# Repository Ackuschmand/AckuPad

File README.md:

# AckuPad

Programmable Makropad based on a Seeed XIAO RP2040 with 6 switches, a toggle switch, an OLED display and a rotary encoder!

---

## Bill of Materials

### Electronics
- 1× Seeed XIAO RP2040  
- 7× MX-Style switches  
  (6× normal buttons, 1× mode button)
- 1× EC11 Rotary encoder  
- 1x 0.91 inch OLED displays  
- 1× PCB  

---

### Mechanical
- 1× 3D printed case (top)  
- 1× 3D printed case (bottom)
- 1× 3D printed case (middle)
- 1× Encoder knob
- 7× Blank DSA keycaps
- 4× M3x16mm screws
- 4× M3x5mx4mm heatset inserts
---

## Notes

- The mode button is a **normal mechanical keyboard switch**
- Buttons and encoder are **PC-controlled**
- Firmware does not contain fixed macros
- Case is fully 3D printed
- Custom PCB is used

---

## Files

- `RP2040 Code.ino` – firmware  
- `AckuPad UI.ahk` – PC script  
- PCB and CAD files are in their respective folders

---

## Pictures

PCB:

Circuit diagram:

Case:

Finished AckuPad:

Youtube video:

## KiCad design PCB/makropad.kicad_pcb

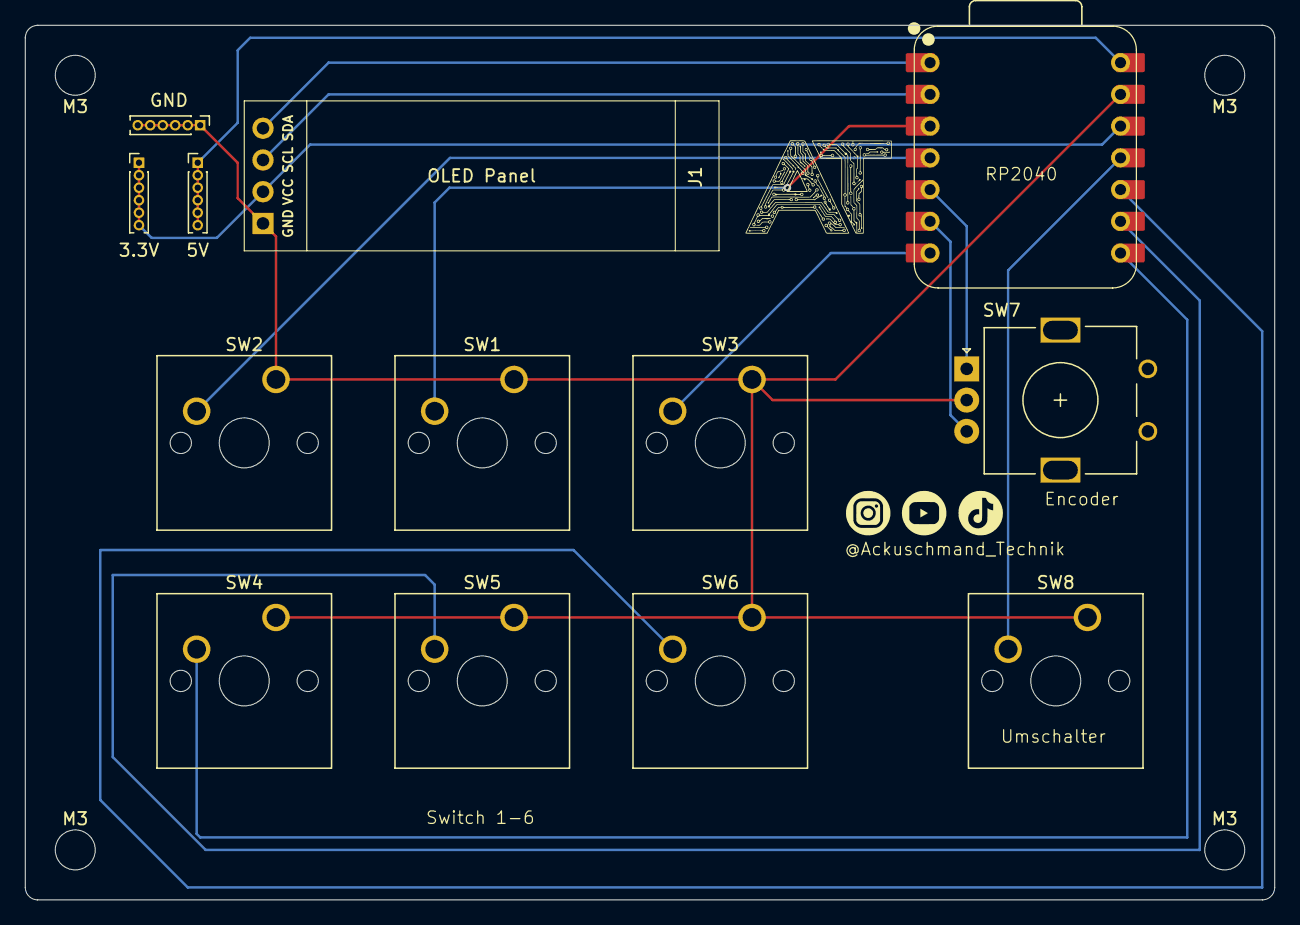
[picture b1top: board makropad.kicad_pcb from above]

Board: 2 copper layers, 100.0 x 70.0 mm, 17 parts (0 on the bottom side), 14 nets.

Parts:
3.3V, 5V: Conn_01x06_Pin; PinHeader_1x06_P1.00mm_Vertical
GND: Conn_01x06_Pin; PinHeader_1x06_P1.00mm_Vertical
J1: Display; SSD1306-0.91-OLED-4pin-128x32
M3, M3#2, M3#3, M3#4: MountingHole_3.2mm_M3
SW1: Switch 1; SW_Cherry_MX_1.00u_PCB
SW2: Switch 2; SW_Cherry_MX_1.00u_PCB
SW3: Switch 3; SW_Cherry_MX_1.00u_PCB
SW4: Switch 4; SW_Cherry_MX_1.00u_PCB
SW5: Switch 5; SW_Cherry_MX_1.00u_PCB
SW6: Switch 6; SW_Cherry_MX_1.00u_PCB
SW7: RotaryEncoder; RotaryEncoder_Alps_EC11E_Vertical_H20mm
SW8: Umschalter; SW_Cherry_MX_1.00u_PCB
U1: XIAO-RP2040-DIP (Mikrocontroller); XIAO-RP2350-DIP

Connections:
+3.3V: 3.3V.1, 3.3V.2, 3.3V.3, 3.3V.4, 3.3V.5, 3.3V.6, J1.2, U1.12 (3V3)
+5V: 5V.1, 5V.2, 5V.3, 5V.4, 5V.5, 5V.6, U1.14 (VBUS)
GND: GND.1, GND.2, GND.3, GND.4, GND.5, GND.6, J1.1, SW1.1, SW2.1, SW3.1, SW4.1, SW5.1, SW6.1, SW7.C, SW8.1, U1.13 (GND)
unnamed: J1.3, U1.2 (GPIO27/ADC1/A1)
unnamed: J1.4, U1.1 (GPIO26/ADC0/A0)
unnamed: SW3.2, U1.7 (GPIO0/TX)
unnamed: SW4.2, U1.8 (GPIO1/RX)
unnamed: SW5.2, U1.9 (GPIO2/SCK)
unnamed: SW8.2, U1.11 (GPIO3/MOSI)
unnamed: SW6.2, U1.10 (GPIO4/MISO)
unnamed: SW7.A, U1.5 (GPIO6/SDA)
unnamed: SW7.B, U1.6 (GPIO7/SCL)
unnamed: SW1.2, U1.3 (GPIO28/ADC2/A2)
unnamed: SW2.2, U1.4 (GPIO29/ADC3/A3)

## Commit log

2026-01-27 Create CAD
2026-01-27 Create CAD1
2026-01-27 Create PCB1
2026-01-27 Create Firmware1
2026-01-27 Create Picture1
2026-01-27 Rename Makropad Boden.stl to Makropad box.stl
2026-01-27 Rename Makropad Deckel.stl to Makropad lid.stl
2026-01-27 Rename RP2040_Code.ino to RP2040 Code
2026-01-27 Create test code (.ahk)
2026-01-27 Rename RP2040 Code to RP2040 Code (.ino)
2026-01-27 Rename test code (.ahk) to test script (.ahk)
2026-01-27 Create Tutorial on programming and electronics
2026-01-28 Rename Makropad.stl to Makropad switch holder.stl
2026-01-29 Create step1
2026-01-29 Create Stl1
2026-01-29 Rename Makropad.stl to Makropad middle.stl
2026-01-29 Rename Makropad Deckel.stl to Makropad topl.stl
2026-01-29 Rename Makropad Boden.stl to Makropad bottom.stl
2026-02-12 Update RP2040 Code (.ino)
2026-02-12 Update and rename test script (.ahk) to AckuPad UI (.ahk)
2026-02-12 Update Tutorial on programming and electronics
2026-02-12 Rename Tutorial on programming and electronics to Tutorial on programming
